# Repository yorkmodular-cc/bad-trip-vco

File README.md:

## York Modular 'Bad Trip' VCO

**This module is now discontinued - there will be no more made unless there is sufficient demand to justify a new run of boards and panels.**

**Information provided here is provided under the terms of the Creative Commons License Attribution-ShareAlike 4.0 International**

These are the files that you may (or may not) need for the Bad Trip VCO kit. It is assumed that you have enough knowledge to source appropriate components and read a schematic. 

Knowledge of how to use the Arduino IDE (or equivalent) to flash an ATTiny45/85 MCU is also desireable but not essential. In order to flash the firmware, your Arduino setup will need to include the ATTiny core by David Mellis - you can download that at https://github.com/damellis/attiny or install it via the Board Manager on newer versions of the Arduino IDE. As is, the default firmware will fit onto an ATTiny45 with space to spare - when flashing the firmware you'll need to specify the appropriate MCU with a 16MHz internal clock. Whilst there's absolutely no reason why you can't use a different clock speed, the frequency lookup table values assume a clock speed of 16MHz

The 'Bad Trip' is a square/saw VCO with a built in resonant vactrol filter - it gets it's name from the fact that you can coax some pretty squonky acid-style basslines out of it on the one hand, and utterly godawful nightmare noises on the other. 

More fun than it sounds, really.

Files included are:

- `badtrip-schematic.png` - the board schematic.
- `badtrip-bom.xlsx` - the Bill of Materials (BOM); this is a list of all the bits you'll need to complete the build.
- The `panels` directory contains design files for the front panel in AutoCAD (`.dxf`) and Schaeffer (`.fpd`) formats. You'll need these if you plan to fab your own panels.
- The `src` directory contains the firmware source file and a corresponding `.hex` file.
- `gerbers` contains the Gerber file for fabrication. These are what you want to be sending to the fab.

The firmware has a permissive license, so feel free to hack on it - all pull requests will be considered.

### Construction

There are no particular gotchas in terms of construction, however you should consider the following when setting the module up:

- Trimmer R7 controls the amount of current flowing into the two filter vactrols.
- Trimmers R10 and R11 affect the 'maximum' resistance of the two filter vactrols. They don't necessarily need to be trimmed to the same value - indeed, you'll get more interesting sounds out if they aren't.
- The effect of the feedback resistor will depend on the values of R10 and R11; in a lot of cases the response is somewhat 'digital' - if you're building from scratch then you can replace this pot with a wire link (and make sure you remove the corresponding hole from the panel)

### IMPORTANT

Since the VCO is microcontroller-based there are limits to the range of CV voltages that can be handled - anything negative is 'rejected' (ie. treated as 0V) whereas anything above 5V is clipped to 5V - the net result is that the VCO has a range of 5 octaves. Under most circumstances you'll want to have the CV pot fully clockwise, however if you're outputting particularly 'hot' CVs then you'll need to fiddle with the CV attenuator to bring the incoming CV down to something that the MCU can handle.

By default, the lowest note output by the VCO is C1 (32Hz) - you can alter this in firmware by modifying the frequency lookup table.

The tracking is pretty decent over 5 octaves but suffers a little due to the resolution of the ATTiny's ADC (10 bits) - this means that the input range is split into 1024 'divisions', with each division corresponding to around 4mV. If you want super-accurate to-the-cent tuning then you might well be disappointed, although you could probably fix things up in the firmware to a certain extent - this is where most of the work is done anyway.

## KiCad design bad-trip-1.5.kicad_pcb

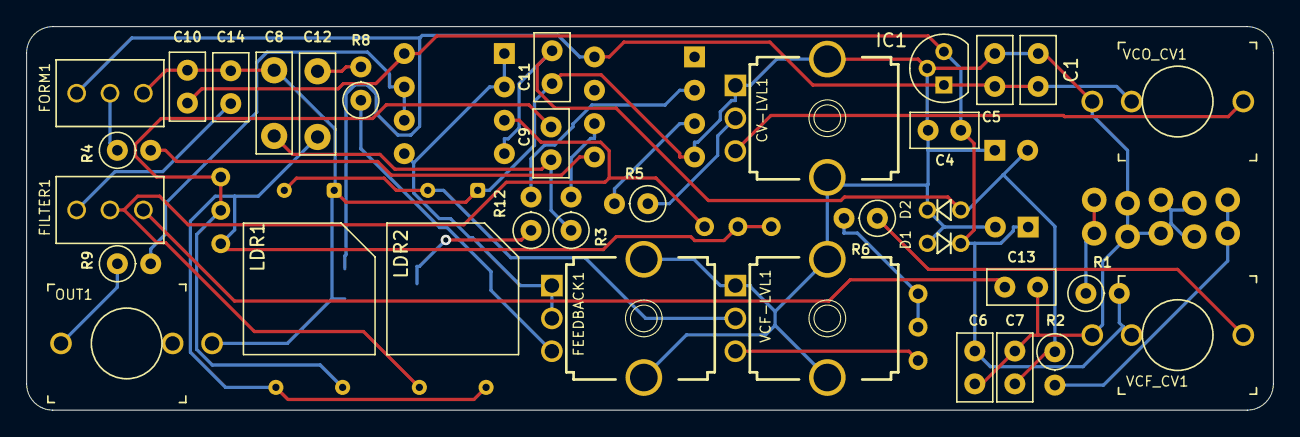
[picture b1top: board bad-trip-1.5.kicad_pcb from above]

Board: 2 copper layers, 94.9 x 29.2 mm, 43 parts (0 on the bottom side), 29 nets.

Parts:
C1, C5, C6, C7, C10, C11: 100n; C_Disc_D5.0mm_W2.5mm_P2.50mm
C2, C3: CP; CP_Radial_D5.0mm_P2.50mm
C4: 330n; C_Disc_D5.0mm_W2.5mm_P2.50mm
C8, C12: 100n; C_Disc_D7.5mm_W2.5mm_P5.00mm
C9: CP; C_Disc_D5.0mm_W2.5mm_P2.50mm
C13: 330p; C_Disc_D5.0mm_W2.5mm_P2.50mm
C14: 1.5n; C_Disc_D5.0mm_W2.5mm_P2.50mm
CV-LVL1: B100k; 9MM_SNAP-IN_POT
D1, D2: 1N4148; D-2.5
FEEDBACK1: B1M; 9MM_SNAP-IN_POT
FILTER1: SUBMINI_SPDT; SUBMINI_TOGGLE
FORM1: SUBMINI_SPDT; SUBMINI_TOGGLE
IC1: 78Z05; TO-92
IC2: TL072P; DIP-8_W7.62mm_Socket
LDR1, LDR2: VACTROL_4PIN; PerkinElmer_VTL5C
LOCK1: EURO_POWER_LOCK; EURO_PWR_HEADER_LOCK
OUT1: THONKICONNNEW; WQP-PJ301M-12_JACK
R1, R2: 22R; R_Axial_DIN0207_L6.3mm_D2.5mm_P2.54mm_Vertical
R3, R8, R9: 1k; R_Axial_DIN0207_L6.3mm_D2.5mm_P2.54mm_Vertical
R4, R12: 10k; R_Axial_DIN0207_L6.3mm_D2.5mm_P2.54mm_Vertical
R5: 22k; R_Axial_DIN0207_L6.3mm_D2.5mm_P2.54mm_Vertical
R6: 100R; R_Axial_DIN0207_L6.3mm_D2.5mm_P2.54mm_Vertical
R7: 20k; Potentiometer_Bourns_3296W_Vertical
R10, R11: 1M; Potentiometer_Bourns_3296W_Vertical
RV1: R_POT; Potentiometer_Bourns_3314G_Vertical
U1: ATTINY85P; DIP-8_W7.62mm_Socket
VCF-LVL1: A100k; 9MM_SNAP-IN_POT
VCF_CV1: THONKICONNNEW; WQP-PJ301M-12_JACK
VCO_CV1: THONKICONNNEW; WQP-PJ301M-12_JACK

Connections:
+5V: C1.2, C5.2, FORM1.1, IC1.1, RV1.3, U1.8, VCO_CV1.P$2_SWITCH
+12V: C2.1, C4.2, C6.2, C10.2, D1.C, IC1.3, IC2.8, R1.2, VCF_CV1.P$2_SWITCH
-12V: C3.2, C7.1, C11.2, D2.A, IC2.4, R2.1
GND: C1.1, C2.2, C3.1, C4.1, C5.1, C6.1, C7.2, C8.1, C10.1, C11.1, C13.2, C14.2, CV-LVL1.1, CV-LVL1.CHASSIS1, CV-LVL1.CHASSIS2, D1.A, D2.C, FEEDBACK1.CHASSIS1, FEEDBACK1.CHASSIS2, FORM1.3, IC1.2, LDR1.1, LDR2.1, LOCK1.GND1, LOCK1.GND2, LOCK1.GND3, LOCK1.GND4, LOCK1.GND5, LOCK1.GND6, OUT1.P$3_SLEEVE, RV1.1, U1.4, VCF-LVL1.1, VCF-LVL1.CHASSIS1, VCF-LVL1.CHASSIS2, VCF_CV1.P$3_SLEEVE, VCO_CV1.P$3_SLEEVE
IN: CV-LVL1.2, R5.1
unnamed: C8.2, C9.2, R3.1
unnamed: C9.1, LDR1.3, R10.2, R10.3
unnamed: C12.1, LDR1.4, LDR2.3, R10.1, R11.2, R11.3
unnamed: C12.2, R8.2
unnamed: C13.1, FILTER1.3
unnamed: C14.1, FILTER1.1
unnamed: CV-LVL1.3, VCO_CV1.P$1_TIP
unnamed: FEEDBACK1.1, FEEDBACK1.2, IC2.1, IC2.2, IC2.5
unnamed: FEEDBACK1.3, R8.1
unnamed: FILTER1.COM, IC2.3, LDR2.4, R11.1
unnamed: FORM1.COM, R4.1
unnamed: IC2.6, IC2.7, R9.2
unnamed: LDR1.2, LDR2.2, VCF-LVL1.2
unnamed: LOCK1.NEG1, LOCK1.NEG2, R2.2
unnamed: LOCK1.POS1, LOCK1.POS2, R1.1
unnamed: OUT1.P$1_TIP, R9.1
unnamed: R4.2, U1.5
unnamed: R5.2, U1.3
unnamed: R6.1, VCF_CV1.P$1_TIP
unnamed: R6.2, R7.2, R7.3
unnamed: R7.1, VCF-LVL1.3
unnamed: R12.1, RV1.2
unnamed: R12.2, U1.2
OUT: R3.2, U1.6

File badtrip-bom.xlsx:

Qty | Value | Device | Package | Parts | Description
1 | 1.5n | C-EU025-025X050 | C025-025X050 | C14 | CAPACITOR, European symbol
1 | 100R | R-EU_0207/2V | 0207/2V | R6 | RESISTOR, European symbol
6 | 100n | C-EU025-025X050 | C025-025X050 | C1, C5, C6, C7, C10, C11 | CAPACITOR, European symbol
2 | 100n | C-EU050-025X075 | C050-025X075 | C8, C12 | CAPACITOR, European symbol
1 | 10k | R-EU_0207/2V | 0207/2V | R4 | RESISTOR, European symbol
3 | 10u | CPOL-EUE2.5-5 | E2,5-5 | C2, C3, C9 | POLARIZED CAPACITOR, European symbol
2 | 1M | R-TRIMM3296W | RTRIM3296W | R10, R11 | Trimm resistor
2 | 1N4148 | DIODE-D-2.5 | D-2.5 | D1, D2 | DIODE
2 | 1k | R-EU_0207/2V | 0207/2V | R3, R9 | RESISTOR, European symbol
1 | 20k | R-TRIMM3296W | RTRIM3296W | R7 | Trimm resistor
2 | 22R | R-EU_0207/2V | 0207/2V | R1, R2 | RESISTOR, European symbol
1 | 22k | R-EU_0207/2V | 0207/2V | R5 | RESISTOR, European symbol
1 | 330n | C-EU025-025X050 | C025-025X050 | C4 | CAPACITOR, European symbol
1 | 330p | C-EU025-025X050 | C025-025X050 | C13 | CAPACITOR, European symbol
1 | 78L05Z | 78L05Z | TO92 | IC1 | Positive VOLTAGE REGULATOR
1 | A100k | 9MM_SNAP-IN_POT_CHASSIS | 9MM_SNAP-IN_POT | VCF-LVL | 9mm vertical snap-in pot, Alpha / Panasonic style, with a connection to the met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
1 | ATTINY85-20P | ATTINY85-20P | PDIP08_300MIL | U1 | ATMEL ATtiny 85
1 | B100k | 9MM_SNAP-IN_POT_CHASSIS | 9MM_SNAP-IN_POT | CV-LVL | 9mm vertical snap-in pot, Alpha / Panasonic style, with a connection to the met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
1 | B1M | 9MM_SNAP-IN_POT_CHASSIS | 9MM_SNAP-IN_POT | FEEDBACK | 9mm vertical snap-in pot, Alpha / Panasonic style, with a connection to the met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
1 | EURO_POWER_LOCK | EURO_POWER_LOCK | EURO_PWR_HEADER_LOCK | LOCK1
2 | SUBMINI_SPDT | SUBMINI_SPDT | SUBMINI_TOGGLE | FILTER, FORM | Subminiature switches – solder pin connections, 2.54mm centres.
3 | THONKICONNNEW | THONKICONNNEW | WQP-PJ301M-12_JACK | OUT, VCF_CV, VCO_CV | 3.5mm socket for Eurorack modular synths
1 | TL072P | TL072P | DIL08 | IC2 | OP AMP
2 | VACTROL_4PIN | VACTROL_4PIN | VACTROL_4PIN_VTL5C | LDR1, LDR2 | 4 Pin Vactrol Resistive Photocoupler
 |  |  |  | NOTES: | C13/C14 are the two ‘main’ filter caps – lower values => ‘harsher’ sound.
 |  |  |  |  | R10 and R11 control the maximum resistance of the vactrols
 |  |  |  |  | R7 controls the current into the vactrols from the CV input – tweak R7, R10 and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
 |  |  |  |  | Feedback pot can be omitted (use wire link) or replaced with a fixed resistor i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

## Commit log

2019-08-12 Module images
2019-09-02 README.md edited online with Bitbucket
2020-02-14 Files for v1.5 revision
2021-04-17 Update README file
2021-04-17 Add Gerber files
2022-05-13 Create LICENSE
